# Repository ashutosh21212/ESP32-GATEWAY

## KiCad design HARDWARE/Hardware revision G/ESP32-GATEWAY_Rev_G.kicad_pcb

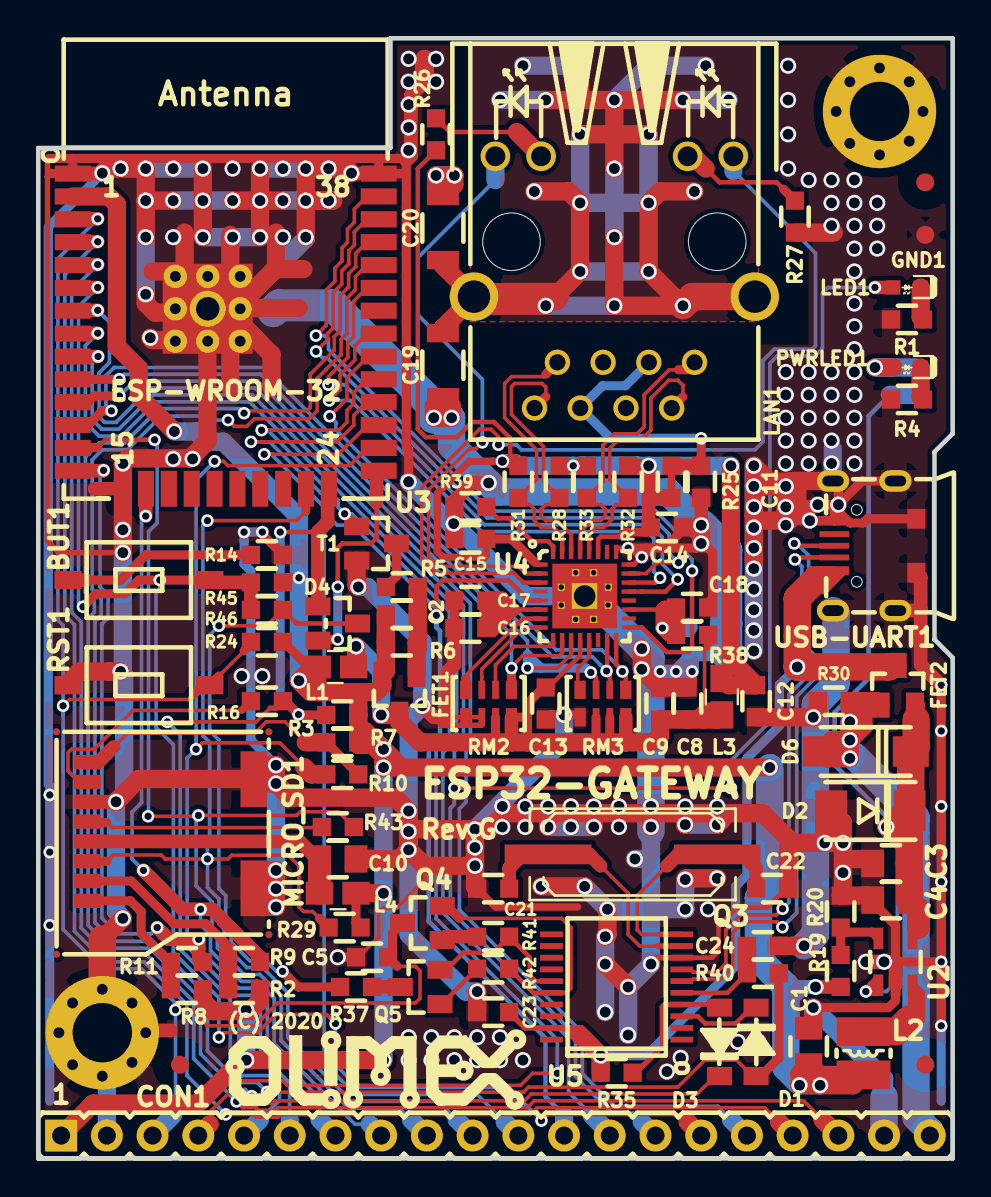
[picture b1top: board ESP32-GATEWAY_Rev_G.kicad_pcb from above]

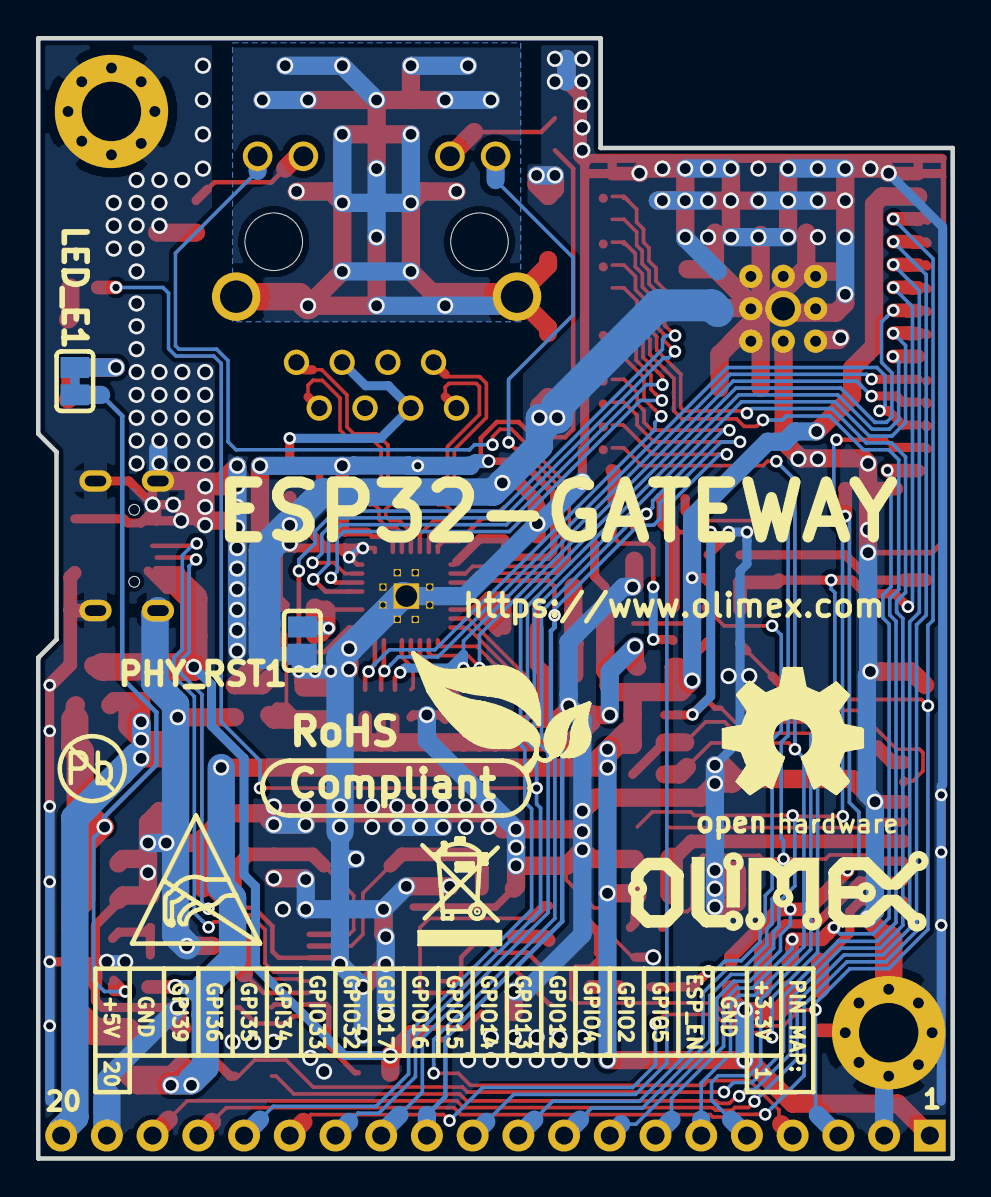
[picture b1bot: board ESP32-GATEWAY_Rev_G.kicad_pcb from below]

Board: 2 copper layers, 50.8 x 62.2 mm, 101 parts (8 on the bottom side), 76 nets.

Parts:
BUT1: T1107A(6x3,8x2,5MM)
C1, C3, C4, C10: 47uF/6.3V/20%/X5R/C0805; C_0805_5MIL_DWS
C2, C8, C9, C12, C23: 22uF/6.3V/20%/X5R/C0603; C_0603_5MIL_DWS
C5: 1uF/C0603; C_0603_5MIL_DWS
C11, C13, C14, C15, C17, C24: 100nF/50V/20%/Y5V/C0603; C_0603_5MIL_DWS
C16: 2.2uF/6.3V/10%/X5R/C0603; C_0603_5MIL_DWS
C18: NA(10uF/6.3V/20%/X5R/C0603); C_0603_5MIL_DWS
C19: 1nF/2000V/10%/X7R/C1206; C_1206_5MIL_DWS_ISO
C20: NA(1nF/2000V/10%/X7R/C1206); C_1206_5MIL_DWS_ISO
C21, C22: 27pF/50V/5%/C0G/C0603; C_0603_5MIL_DWS
CON1: NA(NH1x20); HN1x20
D1, D3: 1N5819S4/SOD123; SOD-123_1C-2A_KA
D2: SMBJ6.0A(DO-214AA); DO214AA_1(K)-2(A)
D4: BAT54C(SOT23-3); SOT23-3
D6: 1N5822/SS34/SMA; SMA-KA
FET1, FET2: WPM2015-3/TR; SOT23
FID1, FID2, FID3: Fiducial; Fiducial1x3
GND1: TESTPAD; TESTPAD_40-ROUND
L1: NA(FB0805/600R/2A); L_0805_5MIL_DWS
L2: 2.2uH/1.5A/DCR=72mR/20%/3.00x3.00x1.50mm/CD32(NR3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; CD32
L3, L4: FB0805/600R/2A; L_0805_5MIL_DWS
LAN1: RJLD-060TC1(LPJ4013EDNL); RJLBC-060TC1
LED1: LED/GREEN/0603; LED_0603_KA
LED_E1: Closed; SJ
Logo-OLimeX: OLIMEX_LOGO_TB
Logo-OSHW: LOGO_OPENHARDWARE_8x8
Logo-vadactroBIG: VADACTRO_LOGO_TB
MH1, MH2: Mounting_hole_Shield_3.3mm
MICRO_SD1: TFC-WXCP11-08-LF
PHY_RST1: Opened; SJ
PWRLED1: LED/RED/0603; LED_0603_KA
Q3: Q12MHz/20pF/30ppm/2P/HC-49SM(SMD); Q_49U3HMS
Q4, Q5: BC817-40(SOT23); SOT23
R1, R2, R3, R4, R7, R8: 2.2k/R0603; R_0603_5MIL_DWS
R5, R41, R42: 1k/R0603; R_0603_5MIL_DWS
R6, R24, R29, R35, R38, R40, R45: 10k/R0603; R_0603_5MIL_DWS
R9, R10, R11, R46: NA/R0603; R_0603_5MIL_DWS
R14, R16, R37: 220R/R0603; R_0603_5MIL_DWS
R19: 220k/R0603; R_0603_5MIL_DWS
R20: 49.9k/1%/R0603; R_0603_5MIL_DWS
R25: 0R(Board_Mounted); R_0603_5MIL_DWS
R26, R27: 330R/R0603; R_0603_5MIL_DWS
R28, R31, R32, R33: 49.9R/1%/R0603; R_0603_5MIL_DWS
R30: 1M/R0603; R_0603_5MIL_DWS
R39: 12.1k/1%/R0603; R_0603_5MIL_DWS
R43: 10R/R0603; R_0603_5MIL_DWS
RM2, RM3: RA1206_(4X0603)_4B8_2.2k; R_MATRIX_4
RST1: T1107A(6x3,8x2,5MM)
Sign-Antistatic: Val**; LOGO_ANTISTATIC_1
Sign-RecyclBin: LOGO_RECYCLEBIN_1
Sign_Pb-Free: LOGO_PBFREE
Sign_RoHS: Val**; LOGO_ROHS_1
T1: DTC114YKA; SOT23
U2: SY8089AAAC(SOT23-5); SOT-23-5
U3: ESP32-WROOM-32D-4MB; ESP-WROOM-32_MODULE
U4: LAN8710A-EZC(QFN32); QFN32_EP(33)_5.00x5.00x0.90mm_Pitch_0.50mm
U5: CH340T(SSOP20W); SSOP-20W
USB-UART1: MISB-SWMM-5B-LF(USB_MICRO); USB-MICRO_MISB-SWMM-5B_LF

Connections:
+3.3VLAN: C8.1, C9.1, C13.1, FET1.3, L1.2, L3.1, R38.2, RM2.3.1, RM2.4.1, RM3.1.2, RM3.2.2, RM3.3.2, U4.12
+3V3: C1.1, C2.1, CON1.1, FET1.2, L1.1, L2.2, L4.1, R2.1, R3.1, R6.1, R7.1, R8.1, R19.2, R24.1, R29.1, R45.1, U3.2
+5V: C3.1, C4.1, D2.1, D6.1, FET2.2, LED_E1.1, LED_E1.2, PWRLED1.2, U2.1, U2.4
+5V_EXT: CON1.20, D6.2, FET2.1, R30.1
/+5V_USB: C23.1, FET2.3, R35.1, U5.19, USB-UART1.1
/D_Com: D4.3, R37.2, R46.2
/ESP_EN: C5.1, CON1.3, Q4.3, R24.2, RST1.1, U3.3
/GPI34\BUT1: BUT1.1, CON1.15, R45.2, R46.1, U3.6
/GPI35: CON1.16, U3.7
/GPI36: CON1.17, U3.4
/GPI39: CON1.18, U3.5
/GPIO0: D4.2, U3.25
/GPIO1\U0TXD: D3.1, U3.35
/GPIO2\HS2_DATA0: CON1.5, D4.1, R3.2, R16.1, U3.24
/GPIO3\U0RXD: D1.2, R40.2, U3.34
/GPIO4\HS2_DATA1: CON1.6, R10.1, U3.26
/GPIO5\PHY_PWR: CON1.4, T1.1, U3.29
/GPIO12\HS2_DATA2: CON1.7, R11.1, U3.14
/GPIO13\HS2_DATA3: CON1.8, R9.1, U3.16
/GPIO14\HS2_CLK: CON1.9, R43.1, U3.13
/GPIO15\HS2_CMD: CON1.10, MICRO_SD1.3, R29.2, U3.23
/GPIO16: CON1.11, U3.27
/GPIO17\EMAC_CLK_OUT_180: CON1.12, U3.28, U4.5
/GPIO18\MDIO(RMII): RM3.1.1, U3.30, U4.16
/GPIO19\EMAC_TXD0(RMII): U3.31, U4.22
/GPIO21\EMAC_TX_EN(RMII): U3.33, U4.21
/GPIO22\EMAC_TXD1(RMII): U3.36, U4.23
/GPIO23\MDC(RMII): U3.37, U4.17
/GPIO25\EMAC_RXD0(RMII): RM3.3.1, U3.10, U4.11
/GPIO26\EMAC_RXD1(RMII): RM2.4.2, U3.11, U4.10
/GPIO27\EMAC_RX_CRS_DV: RM3.2.1, U3.12, U4.15
/GPIO32: CON1.13, U3.8
/GPIO33\LED: CON1.14, LED1.2, U3.9
/PHYAD0: RM3.4.1, U4.13
/PHYAD1: RM2.1.2, U4.7
/PHYAD2: RM2.2.2, U4.8
/RMIISEL: RM2.3.2, U4.9
/VDD1A-2A: C11.1, C12.1, C14.1, C15.1, L3.2, LAN1.3, LAN1.6, R25.1, R25.2, R26.1, R28.1, R31.1, R32.1, R33.1, U4.1, U4.27
/VDDCR: C16.1, C17.1, U4.6
GND: C1.2, C3.2, C4.2, C5.2, C8.2, C9.2, C10.2, C11.2, C12.2, C13.2, C14.2, C15.2, C16.2, C17.2, C18.1, C19.2, C20.2, C21.2, C22.2, C23.2, C24.2, CON1.2, CON1.19, D2.2, GND1.1, MH1.GND1, MH2.GND1, MICRO_SD1.6, MICRO_SD1.SH1, MICRO_SD1.SH2, PHY_RST1.1, R1.1, R4.2, R14.2, R20.2, R27.2, R30.2, R39.2, RM2.1.1, RM2.2.1, RM3.4.2, RST1.2, T1.2, U2.2, U3.1, U3.15, U3.38, U3.39, U4.24, U4.25, U4.33, U5.8, USB-UART1.0, USB-UART1.5
unnamed: BUT1.2, R14.1
unnamed: C2.2, FET1.1, R5.1, R6.2
unnamed: C10.1, L4.2, MICRO_SD1.4
unnamed: C18.2, PHY_RST1.2, R38.1, U4.19
unnamed: C19.1, C20.1, LAN1.GND1, LAN1.GND2
unnamed: C21.1, Q3.1, U5.9
unnamed: C22.1, Q3.2, U5.10
unnamed: C24.1, R40.1, U5.5
unnamed: D1.1, U5.3
unnamed: D3.2, R35.2, U5.4
unnamed: L2.1, U2.3
unnamed: LAN1.1, R33.2, U4.29
unnamed: LAN1.2, R32.2, U4.28
unnamed: LAN1.7, R31.2, U4.31
unnamed: LAN1.8, R28.2, U4.30
unnamed: LAN1.AG1, R26.2
unnamed: LAN1.AY1, U4.3
unnamed: LAN1.KG1, U4.2
unnamed: LAN1.KY1, R27.1
unnamed: LED1.1, R1.2
unnamed: MICRO_SD1.1, R8.2, R11.2
unnamed: MICRO_SD1.2, R2.2, R9.2
unnamed: MICRO_SD1.5, R43.2
unnamed: MICRO_SD1.7, R16.2
unnamed: MICRO_SD1.8, R7.2, R10.2
unnamed: PWRLED1.1, R4.1
unnamed: Q4.1, R41.2
unnamed: Q4.2, R42.1, U5.16
unnamed: Q5.1, R42.2
unnamed: Q5.2, R41.1, U5.15
unnamed: Q5.3, R37.1
unnamed: R5.2, T1.3
unnamed: R19.1, R20.1, U2.5
unnamed: R39.1, U4.32
unnamed: U5.6, USB-UART1.3
unnamed: U5.7, USB-UART1.2

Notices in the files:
HARDWARE/Hardware revision G/ESP32-GATEWAY_Rev_G.kicad_pcb:
(C) 2020
